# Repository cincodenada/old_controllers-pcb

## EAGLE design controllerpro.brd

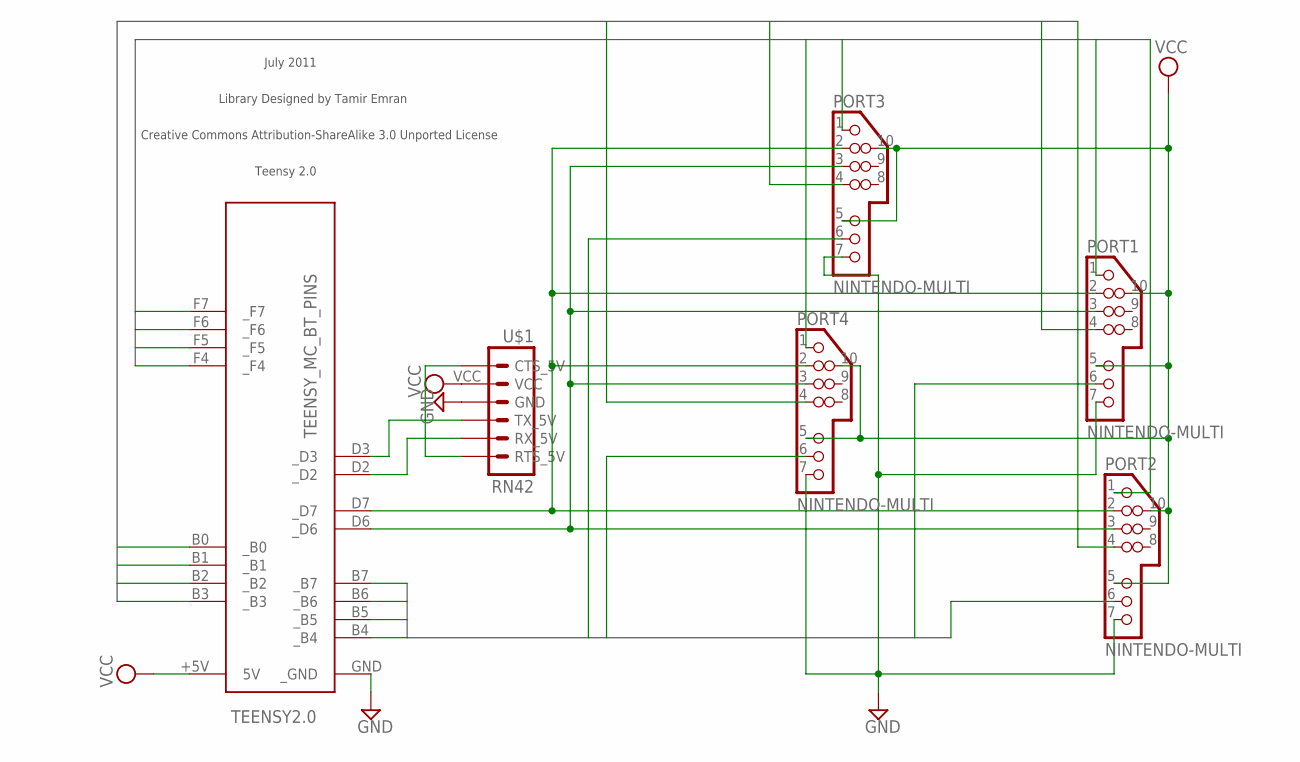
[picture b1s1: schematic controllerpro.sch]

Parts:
PORT1, PORT2, PORT3, PORT4: NINTENDO-MULTI
TEENSY2.0: TEENSY_MC_BT_PINS
U$1: RN42

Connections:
3VDATA0: PORT3.6, TEENSY2.0.B6 (_B6)
3VDATA1: PORT4.6, TEENSY2.0.B7 (_B7)
3VDATA2: PORT1.6, TEENSY2.0.B4 (_B4)
3VDATA3: PORT2.6, TEENSY2.0.B5 (_B5)
5VDATA0: PORT3.4, TEENSY2.0.B2 (_B2)
5VDATA1: PORT4.4, TEENSY2.0.B3 (_B3)
5VDATA2: PORT1.4, TEENSY2.0.B0 (_B0)
5VDATA3: PORT2.4, TEENSY2.0.B1 (_B1)
CLOCK: PORT1.2, PORT2.2, PORT3.2, PORT4.2, TEENSY2.0.D7 (_D7)
GND: PORT1.7, PORT2.7, PORT3.7, PORT4.7, TEENSY2.0.GND (_GND), U$1.GND
LATCH: PORT1.3, PORT2.3, PORT3.3, PORT4.3, TEENSY2.0.D6 (_D6)
unnamed: TEENSY2.0.D2 (_D2), U$1.RX-I (RX_5V)
unnamed: TEENSY2.0.D3 (_D3), U$1.TX-0 (TX_5V)
unnamed: U$1.CTS-I (CTS_5V), U$1.RTS-0 (RTS_5V)
S_OR_NES0: PORT3.1, TEENSY2.0.F6 (_F6)
S_OR_NES1: PORT4.1, TEENSY2.0.F7 (_F7)
S_OR_NES2: PORT1.1, TEENSY2.0.F4 (_F4)
S_OR_NES3: PORT2.1, TEENSY2.0.F5 (_F5)
VCC: PORT1.5, PORT1.10, PORT2.5, PORT2.10, PORT3.5, PORT3.10, PORT4.5, PORT4.10, TEENSY2.0.+5V (5V), U$1.VCC

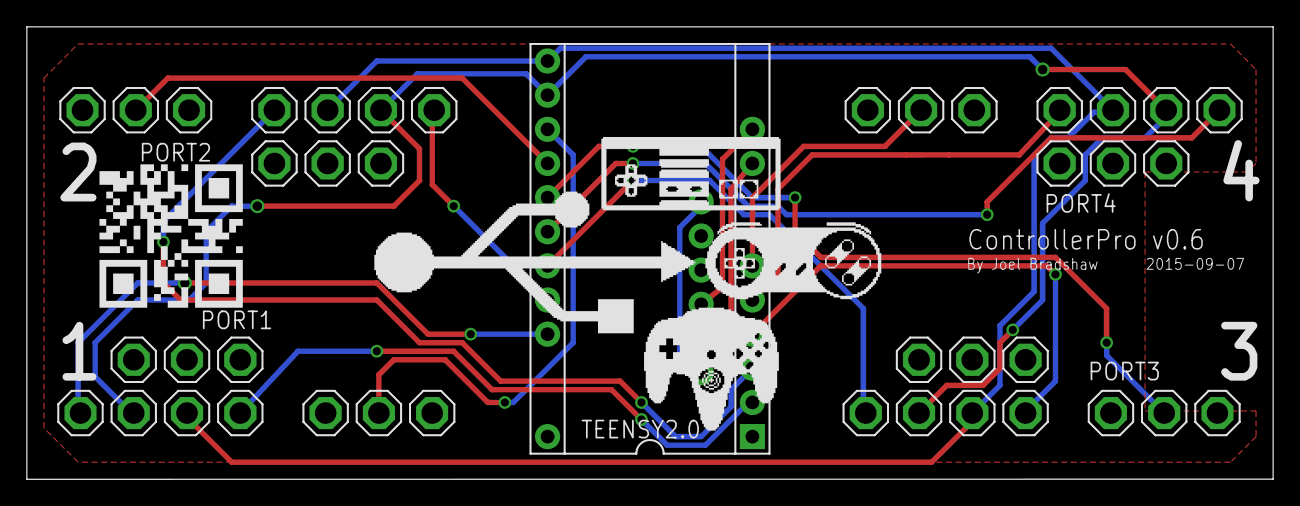
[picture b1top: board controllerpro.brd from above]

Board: 2 copper layers, 92.7 x 33.7 mm, 6 parts (1 on the bottom side), 19 nets.

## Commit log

2013-08-09 Initial layout and such
2013-08-15 Now smaller! Rearranged things to minimize size
    Mostly to reduce board cost, but hey!
2013-08-15 Add my custom teensy parts to the custom library
    Just removed the unneeded pins, we'll just be using two headers
2013-08-17 Widening power traces, adding alignment check vias
2013-09-07 Adding some net names, connecting a missing GND
2013-09-21 Add OpenSCAD model
2013-09-21 Expanding, layout 1
2013-09-21 Expanding, layout 2 (2x2) (1.525x3.275)
2013-09-21 Updated OpenSCAD model
2013-09-21 Working on 2x2 board with teensy straddling N64
2013-09-21 Using only needed pins, also starting on wires
2013-09-21 Using only needed pins
2013-09-21 Teensy in the middle of 2x2 (rotated)
2013-09-21 All wired up (intially)!
2013-09-21 Hiding layout bits, starting on actual box
2013-09-21 Expanding via mirroring every other controller
2013-09-22 Trying to actually line up box with board
2013-09-22 Rerouting some stuff to shrink and center board
    Updating model with new board dimensions and finishing
    re-specfiying controller positions. Yay!
2013-09-26 Adding pull-up resistors
2013-09-26 Conforming box model to actual board, and adding pins
2013-09-26 Moving controllers father away from the teensy
    Avoiding socket collisions per model
2013-09-26 Adding some images/renders
2013-09-26 Fixing images because OpenSCAD can't render properly
2013-09-29 Finishing moving controller ports closer together
    Also added plugin spot on model
2013-09-29 Separate connector-top thing out
2013-09-29 Refactoring things a good bit
    Extracting bits of code into sensible files
2013-09-29 Adding holders to the model
    Gonna run into socket problems though...hmm.
2013-09-29 Re-working the top/bottom grabbers a little
2013-09-30 Fixing the bothsides() function
2013-09-30 Tweaking and adding clickers to the holders
2013-10-06 Adding extra headers to the teensy
    Also tweaking board width
    And adding detail to headers (for printing just sockets)
2013-10-08 Converting to mm, redoing some measurements
    Now I have actual calipers!
2013-10-08 Adding some datasheets and generated STLs
2013-10-08 Updating NES/SNES controller definitions
    Now they actually use my measurements...
2013-10-16 Reworking the top/bottom halves, filling in socket gaps
    Moving to half/half to work around socket walls.
    Lots of reworking of the Teensy socket,
    also adjusting for Teensy pin offset
    which might be troublesome
2013-11-17 Flipping the extra pins, adding board module
    Also fixed linenum script (maybe) and added animation stuff
2013-11-17 Updating STLs
2013-11-18 Making connector cutout wall thicker
    Also adding feet to the bottom and updating STLs
2013-12-30 Adding silkscreens, finalizing for OSH Park
2013-12-31 Flipping Teensy...argh
2013-12-31 Updating rev info
2014-08-07 Shorten bottom sides to make room for the top piece
2014-08-07 Add some clearances
2014-08-07 Add some clearance, and do more fudging
    Also separate out the fudging from the actual values
2014-11-06 Remove IC switches, just use two lines from the µc
2014-11-13 Post-rebase cleanup of boardfile
2014-11-13 Update version date
2014-11-14 Rename ports, add silkscreen port numbers
2014-11-14 Add QR code
2014-11-14 Fix 3
2014-11-14 Update date and move up a bit
2014-11-17 pin_base -> pin_base_height
2014-11-17 Greatly simplify grabbers
2014-11-17 Add board_top helper variable
    Seriously, why did I not do this yet
2014-11-17 Make Teensy push the ceiling up if need be
    And use socket_thick so pin_gap is actually accurate
    Had to rework the connector_cap a good bit, it's a bit awkward now
    but should work fine
2014-12-13 Move box top down, generalize both* functions
2015-08-02 Update board for Bluetooth module
2015-08-02 Connect bluetooth power, etc:
2015-09-07 Switch VCC to 3.3v
    Remove VREG, supply NES/SNES and N64 all with 3.3v
2015-09-07 Do some basic simplifications afforded by 3.3V switch
2015-09-07 Shrink drills for controller pins
2015-09-07 Tighten up keepout lines for pins
2015-09-07 Rework wires on right side for BT antenna
    With new space between pins, we can rearrange a bit
    And completely clear out the space under the BT antenna
2015-09-07 Remove pull-up resistors for N64
    Not necessary any more now that Teensy is at 3.3v
2015-09-07 Some further simplifications/improvements
    Mainly better connecting the ground/power planes
2015-09-07 Update RN42 and move to our custom lib
    Get the footprint/silkscreen on the right side and things
2015-09-07 Update version number and date
2015-09-07 Fix layers for port pins
2015-09-07 Actually, move all pins to tDocu layer
    Shouldn't be silkscreened, consistent with other packages
2018-03-31 Initial commit from import
2018-03-31 Align board to grid, add border for small board
2018-03-31 Add headers, lots of rearranging/tidying
2018-03-31 Shorted connectors to test connectivity
2018-03-31 Revert "Shorted connectors to test connectivity"
    This reverts commit bff4c321492e34593da7785c8a90028fe11ea69b.
2018-04-01 Match footprints and re-label
2018-04-01 Move second set of multiports
2018-04-01 Start laying out board
2018-04-01 More layout
2018-04-01 Remove stray vcc labels
2018-04-01 Make it default to configurable SNES/NES
2018-04-01 Finish initial layout of first port
2018-04-01 Fix port numbers
    That was annoying, but fine
2018-04-01 Place remainder of big footprints
    Resistors still to do
2018-04-01 Clear out existing tracks
2018-04-01 Connect first two terminals (the easy ones)
2018-04-01 Initial complete connection
2018-04-01 Scootch the connectors closer
    They're the constraining factor here
2018-04-01 First attempt at shrinking board
2018-04-01 Tie up loose ends from shrinking board
2018-04-01 Fix misalignment/non-centering of pins
2018-04-01 Add keepout for bluetooth
2018-04-01 Make daughterboards smaller
2018-04-01 Attempt to add zones to daughterboard
2018-04-01 Work on zones on daughterboards
    Still some figuring to do
2018-04-08 Update headers with actual footprint
2018-04-08 Update resistor placement
2018-04-08 Import solder jumpers from Teensy
    Better than caps/resistors
2018-04-08 Set up DRCs for OSHPark
2018-04-08 Move measurements to Dwg layer
    WTF silkscreens
2018-04-08 Switch Teensy package
2018-04-08 Fix pins on new Teensy
2018-04-08 Update boardfile
2018-04-08 Fix board
2018-08-09 Remove duplicate board, add cutouts
2018-08-09 Update to new libraries and fix buses
2018-08-09 Remove second board from schematic
2019-02-05 Add pulldown resistors, shrink child board
2019-02-05 Switch to Teensy 3.2 footprint
2019-02-05 More 3.2 adjustments
    Make it Teensy2 compatible even, hopefully!
2019-02-05 Switch to solder bridges for the SNES mode selectors
2019-02-06 Make controller pin holes smaller
    Finally found a datasheet that recommends a reasonable size
2019-02-06 Shrink top board considerably
    So much empty space!
2019-02-06 Make the bottom board smaller!
    SMALLER SMALLER SMALLER
2019-02-06 Silkscreen!!
    Logos! Labels!
2019-02-08 Nudge bluetooth, refining silkscreen/labels
2019-02-18 Fixes from hardware debugging
    Connect daughterboards to ground (!)
2019-02-18 Split LATCH into four
    Also fix misplaced NES VCC (!!) and ports
2019-02-18 Make power traces thicker
2019-03-14 More tidying
2019-03-14 Manually rename ports
    Also match board by timestamp, nice!
    perl -p -i -e 's/\b(PORT|S|P|5VDATA|3VDATA|S_OR_NES|LATCH)1\b/${1}4/g' *
    perl -p -i -e 's/\b(PORT|S|P|5VDATA|3VDATA|S_OR_NES|LATCH)2\b/${1}1/g' *
    perl -p -i -e 's/\b(PORT|S|P|5VDATA|3VDATA|S_OR_NES|LATCH)3\b/${1}2/g' *
    perl -p -i -e 's/\b(PORT|S|P|5VDATA|3VDATA|S_OR_NES|LATCH)0\b/${1}3/g' *
    perl -p -i -e 's/\b(PORT|S|P|5VDATA|3VDATA|S_OR_NES|LATCH)\[0..3\]/${1}[1..4]/g' *
2019-03-14 Re-add silkscreens
2019-03-15 Silkscreen tweaks
2019-03-15 Fix a needlessly squiggly trace
2019-08-03 Add missing library
2019-08-03 Add a couple more measurements
2019-08-03 Add child board heirarchical sheet
2019-08-04 Move back to one latch, instead try current detect
2019-08-04 Fix connector orientation, get rid of tabs
2019-08-04 Move RN42 board
    It's on top which is great but needs to be out from under the Teensy
2019-08-04 Switch S_OR_NES and DETECT
    So we can do analog measurements on DETECT
    Abandon running wider lines for these, it'll probably be fine
2019-08-05 Connect AGND
2019-08-05 Rename a bunch of stuff, switch DETECT back
2019-08-05 Move things around so everything that needs touch has it
2019-08-09 Fix the board up after moving all the pins around
2019-08-09 Fuck the schematic all up
2019-08-09 Start repairs
2019-08-09 Finish reworking all the things
2019-08-09 Use local labels instead of global and add NCs
2019-08-09 I don't even know what I did this time
2019-08-09 Silkscreen updates, tiny tweaks
2019-08-13 Add optional pulldown resistors
    Just in case, doesn't hurt to have 'em
2019-08-16 Make child boards flippable
    A little bigger, but hopefully only temporarily
2019-08-16 Connect remaining inputs to child boards
    They don't do anything yet, but why not futureify it
2019-08-17 Flip alternate headers
    Would have made the controllers upside-down again
2019-08-28 Initial rejiggering for 5V enable
2019-08-28 Rework connections on child boards only
2019-10-07 Update board
    I don't know why this didn't pick up the first time
2019-10-07 Add mounting holes, update to 0.8.2
2019-10-10 Update silkscreens
2019-10-10 Don't connect extra VCC by default
2019-10-11 Fix mapping and ports
    God, what a mess
2019-10-11 Make trace less circuitous
2019-10-11 Make version 0.9
    We've changed enough here
2019-10-11 Tidy up refs
2019-10-24 Initial building docs
    Seeing if this shows up like I want it to
2019-10-24 Fix headers and image paths
2019-10-24 Add the rest of the docs and a buncha images
2019-10-24 Fix some words
2019-10-24 More image updates
2019-10-24 More typos, fix order of clips, rotate overhang
2019-10-25 Text updates, add link to STL for jig
2019-10-26 Add firmware info
2019-10-26 page
2019-10-28 Link to GitHub release instead of awkward Hackster
2021-11-14 Add .gitignore and logos

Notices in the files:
parts and their libraries:
custom: Licensed Under Creative Commons
custom: Creative Commons Attribution-ShareAlike 3.0 Unported License
